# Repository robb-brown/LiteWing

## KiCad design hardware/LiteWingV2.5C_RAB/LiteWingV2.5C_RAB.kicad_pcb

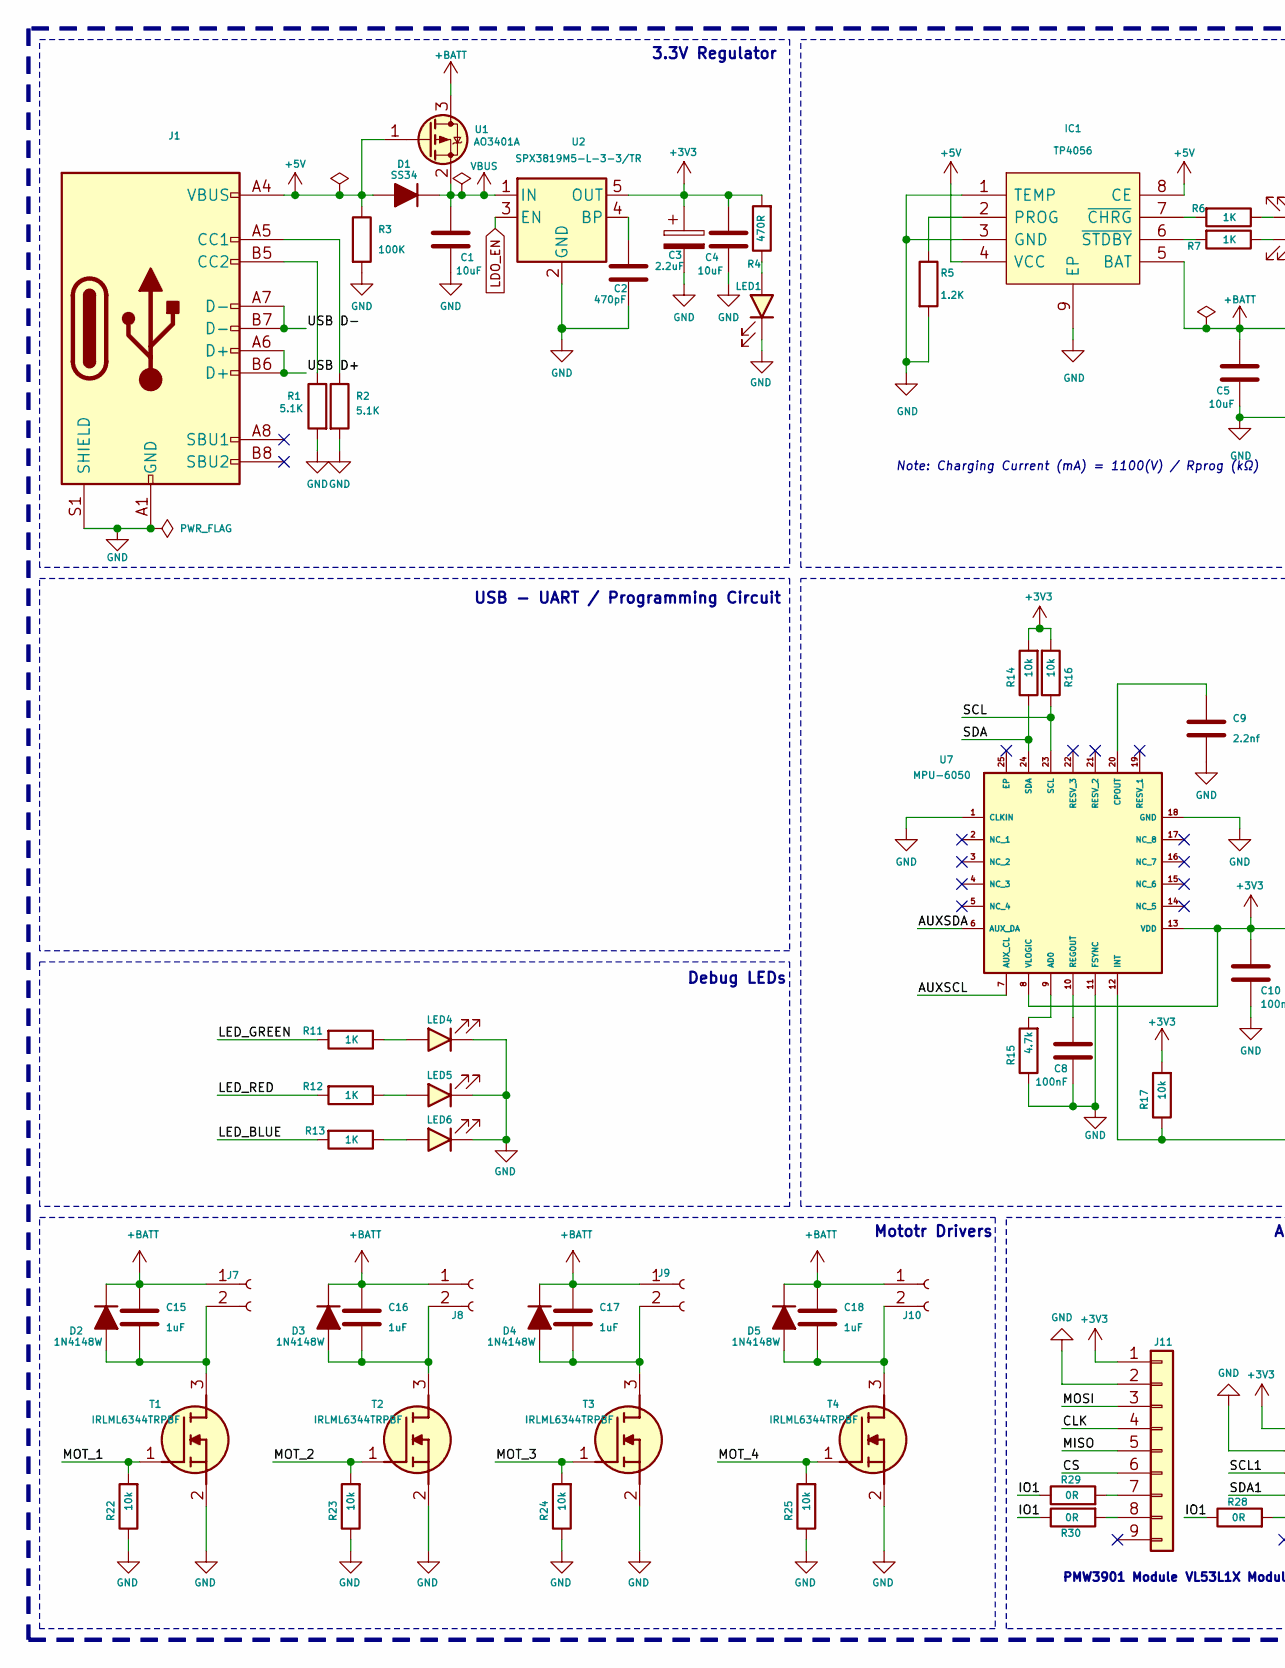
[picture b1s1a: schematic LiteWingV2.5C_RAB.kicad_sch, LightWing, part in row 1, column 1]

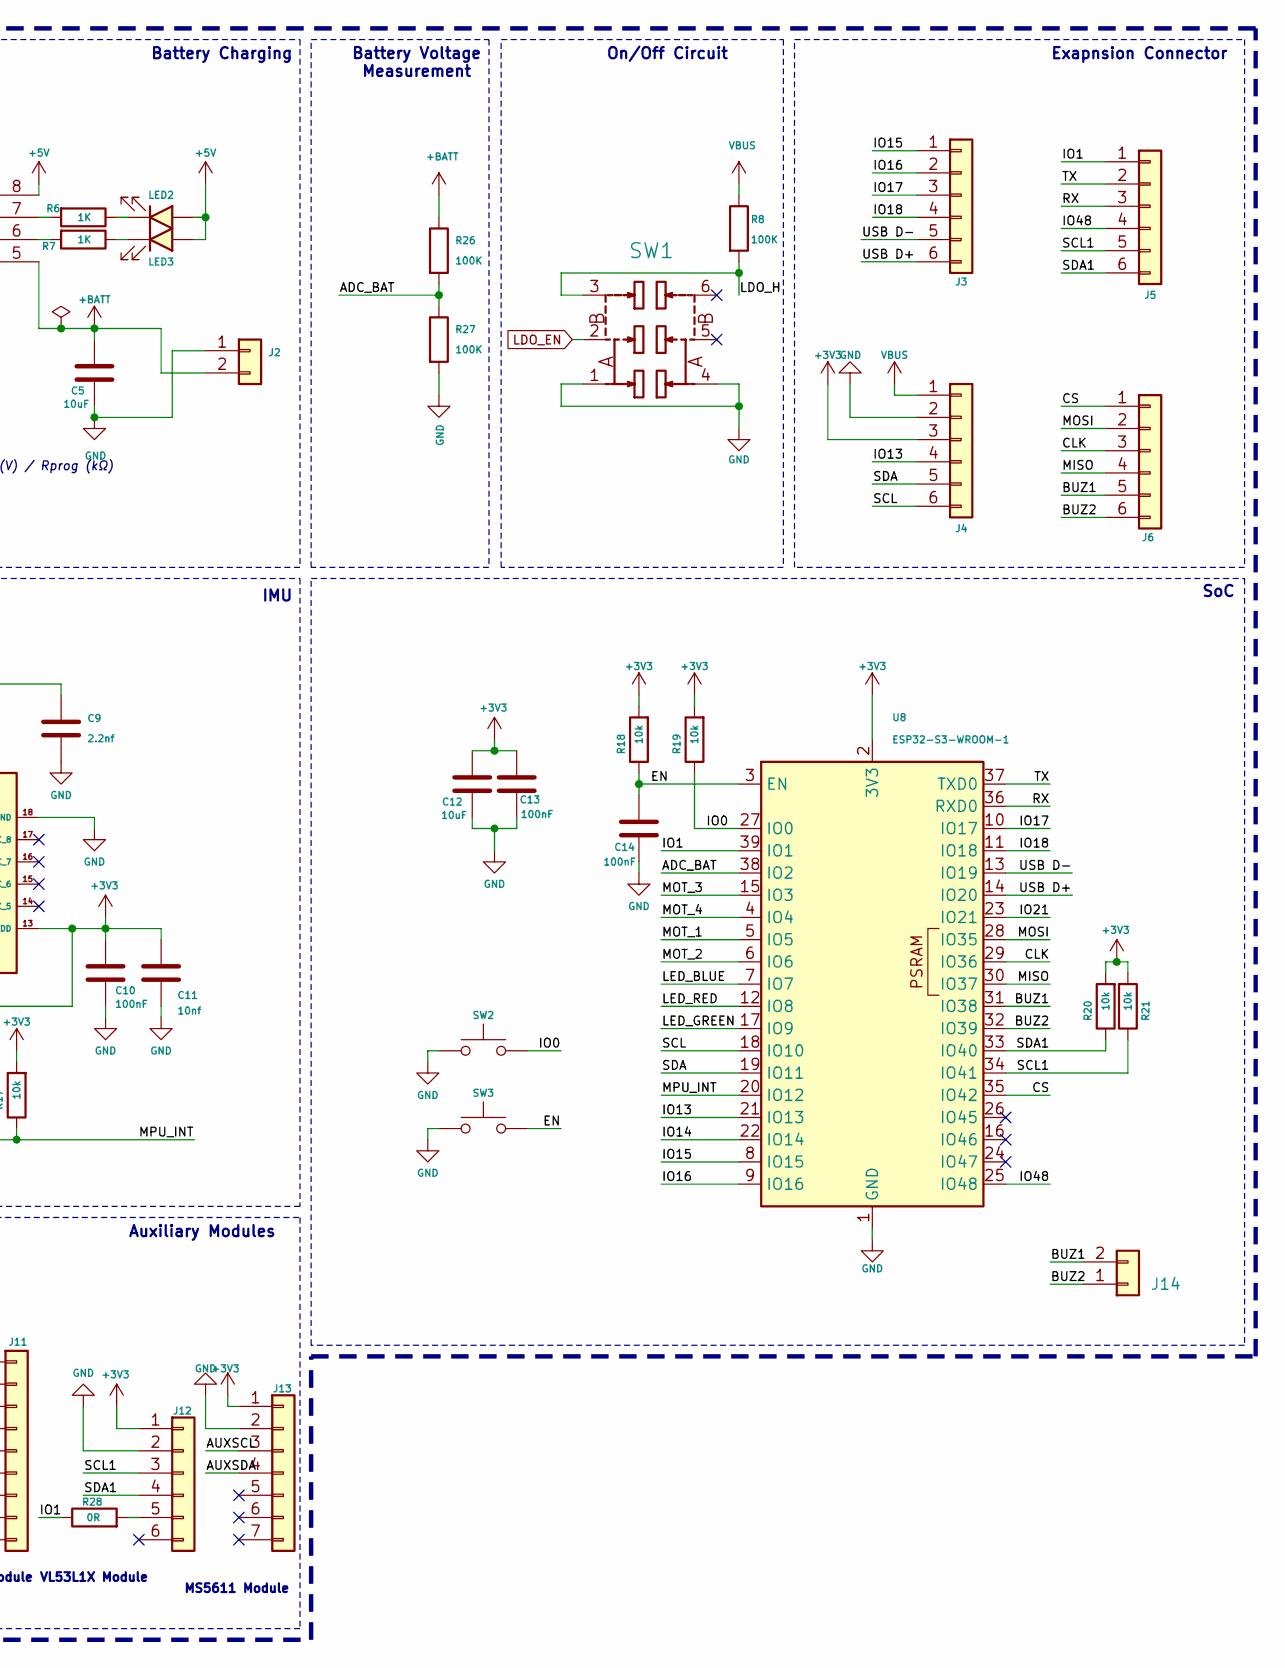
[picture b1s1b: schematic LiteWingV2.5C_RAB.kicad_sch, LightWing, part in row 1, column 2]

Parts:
C1, C4, C5, C12: 10uF; C_0603_1608Metric; MFR.Part # CL10A106KP8NNNC; LCSC Part # C19702
C2: 470pF; C_0603_1608Metric; MFR.Part # 0603B471K500NT; LCSC Part # C1620
C3: 2.2uF; C_0805_2012Metric; MFR.Part # TCC0805X7R225M250FT; LCSC Part # C5448893
C8, C10, C13, C14: 100nF; C_0603_1608Metric; MFR.Part # CC0603KRX7R9BB104; LCSC Part # C14663
C9: 2.2nf; C_0603_1608Metric; MFR.Part # 0603B222K500NT; LCSC Part # C1604
C11: 10nf; C_0603_1608Metric; MFR.Part # 0603B103K500NT; LCSC Part # C57112
C15, C16, C17, C18: 1uF; C_0603_1608Metric; MFR.Part # CL10A105KB8NNNC; LCSC Part # C15849
D1: SS34; D_SMA; MFR.Part # SS34; LCSC Part # C8678
D2, D3, D4, D5: 1N4148W; D_SOD-123F; MFR.Part # 1N4148W; LCSC Part # C81598
IC1: TP4056; SOIC127P600X175-9N; MFR.Part # TP4056; LCSC Part # C20199357
J1: USB_C_Receptacle_USB2.0_16P; USB_C_Receptacle_G-Switch_GT-USB-7010ASV; LCSC Part # C2988369
J2: JST XH 2P 2.50mm SMD Hoz; CONN-TH_2P-P2.50_XH-2AW; MFR.Part # XH-2AW; LCSC Part # C33132
J3, J4, J5, J6: Conn_01x06; PinHeader_1x06_P2.54mm_Vertical
J7, J8, J9, J10: Conn_01x02_Female; JST_PH_B2B-PH-K_1x02_P2.00mm_Vertical
J11: Conn_01x09; PMW3901
J12: Conn_01x06; VL53L1X_BREAKOUT
J13: Conn_01x07; MS5611_Module
J14: Conn_01x02; CONN-TH_1.25T-2A_1.25T-2A; MFR.Part # 1.25-2A; LCSC Part # C722594
LED1, LED2, LED5: LED_Red; LED_0603_1608Metric; MFR.Part # KT-0603R; LCSC Part # C2286
LED3, LED6: LED_Blue; LED_0603_1608Metric; MFR.Part # KT-0603B; LCSC Part # C2288
LED4: LED_Green; LED_0603_1608Metric; MFR.Part # LTST-C193TGKT-5A; LCSC Part # C12065
R1, R2: 5.1K; R_0603_1608Metric; MFR.Part # 0603WAF5101T5E; LCSC Part # C23186
R3, R8, R26, R27: 100K; R_0603_1608Metric; MFR.Part # 0603WAF1003T5E; LCSC Part # C25803
R4: 470R; R_0603_1608Metric; MFR.Part # 0603WAF4700T5E; LCSC Part # C23179
R5: 1.2K; R_0603_1608Metric; MFR.Part # 0603WAF1201T5E; LCSC Part # C22765
R6, R7, R11, R12, R13: 1K; R_0603_1608Metric; MFR.Part # 0603WAF1001T5E; LCSC Part # C21190
R14, R16, R17, R18, R19, R20, R21, R22, R23, R24, R25: 10k; R_0603_1608Metric; MFR.Part # 0603WAF1002T5E; LCSC Part # C25804
R15: 4.7k; R_0603_1608Metric; MFR.Part # 0603WAF4701T5E; LCSC Part # C23162
R28, R29, R30: 0R; R_0603_1608Metric; MFR.Part # 0603WAF0000T5E; LCSC Part # C21189
SW1: MST22D18G2_125; SW-SMD_MST22D18G2; MFR.Part # MST22D18G2 125; LCSC Part # C2906280
SW2, SW3: Tactile Switch 3x4x2; Tactile 3x4x2mm TS-A010; MFR.Part # TS-KG88C-ART25F; LCSC Part # C2874433
T1, T2, T3, T4: IRLML6344TRPBF; SOT95P237X112-3N; MFR.Part # IRLML6344TRPBF-HXY; LCSC Part # C6285738
U1: AO3401A; SOT-23; MFR.Part # AO3401A; LCSC Part # C15127
U2: SPX3819M5-L-3-3/TR; SOT-23-5; MFR.Part # SPX3819M5-L-3-3/TR; LCSC Part # C9055
U7: MPU-6050; MPU6050; MFR.Part # MPU-6050; LCSC Part # C24112
U8: ESP32-S3-WROOM-1; MFR.Part # ESP32-S3-WROOM-1-N8; LCSC Part # C2913198

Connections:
+3V3: C3.1, C4.1, C10.1, C11.1, C12.1, C13.1, J4.3, J11.1, J12.1, J13.1, R4.2, R14.2, R16.2, R17.2, R18.2, R19.2, R20.2, R21.2, U2.5 (OUT), U7.8 (VLOGIC), U7.13 (VDD), U8.2 (3V3)
+5V: D1.2 (A), IC1.4 (VCC), IC1.8 (CE), J1.A4 (VBUS), J1.A9 (VBUS), J1.B4 (VBUS), J1.B9 (VBUS), LED2.2 (A), LED3.2 (A), R3.1, U1.1 (G)
+BATT: C5.1, C15.1, C16.1, C17.1, C18.1, D2.1 (K), D3.1 (K), D4.1 (K), D5.1 (K), IC1.5 (BAT), J2.2, J7.1, J8.1, J9.1, J10.1, R26.1, U1.3 (D)
/ADC_BAT: R26.2, R27.1, U8.38 (IO2)
/AUXSCL: J13.3, U7.7 (AUX_CL)
/AUXSDA: J13.4, U7.6 (AUX_DA)
/BUZ1: J6.5, J14.2, U8.31 (IO38)
/BUZ2: J6.6, J14.1, U8.32 (IO39)
/CLK: J6.3, J11.4, U8.29 (IO36)
/CS: J6.1, J11.6, U8.35 (IO42)
/EN: C14.1, R18.1, SW3.2, U8.3 (EN)
/IO0: R19.1, SW2.2, U8.27 (IO0)
/IO1: J5.1, R28.1, R29.1, R30.1, U8.39 (IO1)
/IO13: J4.4, U8.21 (IO13)
/IO14: U8.22 (IO14)
/IO15: J3.1, U8.8 (IO15)
/IO16: J3.2, U8.9 (IO16)
/IO17: J3.3, U8.10 (IO17)
/IO18: J3.4, U8.11 (IO18)
/IO21: U8.23 (IO21)
/IO48: J5.4, U8.25 (IO48)
/LDO_H: R8.2, SW1.3
/LED_BLUE: R13.2, U8.7 (IO7)
/LED_GREEN: R11.2, U8.17 (IO9)
/LED_RED: R12.2, U8.12 (IO8)
/MISO: J6.4, J11.5, U8.30 (IO37)
/MOSI: J6.2, J11.3, U8.28 (IO35)
/MOT_1: R22.2, T1.1 (G), U8.5 (IO5)
/MOT_2: R23.2, T2.1 (G), U8.6 (IO6)
/MOT_3: R24.2, T3.1 (G), U8.15 (IO3)
/MOT_4: R25.2, T4.1 (G), U8.4 (IO4)
/MPU_INT: R17.1, U7.12 (INT), U8.20 (IO12)
/RX: J5.3, U8.36 (RXD0)
/SCL: J4.6, R16.1, U7.23 (SCL), U8.18 (IO10)
/SCL1: J5.5, J12.3, R21.1, U8.34 (IO41)
/SDA: J4.5, R14.1, U7.24 (SDA), U8.19 (IO11)
/SDA1: J5.6, J12.4, R20.1, U8.33 (IO40)
/TX: J5.2, U8.37 (TXD0)
/USB D+: J1.A6 (D+), J1.B6 (D+), J3.6, U8.14 (IO20)
/USB D-: J1.A7 (D-), J1.B7 (D-), J3.5, U8.13 (IO19)
GND: C1.2, C2.2, C3.2, C4.2, C5.2, C8.2, C9.2, C10.2, C11.2, C12.2, C13.2, C14.2, IC1.1 (TEMP), IC1.3 (GND), IC1.9 (EP), J1.A1 (GND), J1.A12 (GND), J1.B1 (GND), J1.B12 (GND), J1.S1 (SHIELD), J2.1, J4.2, J11.2, J12.2, J13.2, LED1.1 (K), LED4.1 (K), LED5.1 (K), LED6.1 (K), R1.2, R2.2, R3.2, R5.2, R15.1, R22.1, R23.1, R24.1, R25.1, R27.2, SW1.1, SW1.4, SW2.1, SW3.1, T1.2 (S), T2.2 (S), T3.2 (S), T4.2 (S), U2.2 (GND), U7.1 (CLKIN), U7.11 (FSYNC), U7.18 (GND), U8.1 (GND), U8.40 (GND), U8.41 (GND)
LDO_EN: SW1.2, U2.3 (EN)
unnamed: C15.2, D2.2 (A), J7.2, T1.3 (D)
unnamed: C16.2, D3.2 (A), J8.2, T2.3 (D)
unnamed: C17.2, D4.2 (A), J9.2, T3.3 (D)
unnamed: C18.2, D5.2 (A), J10.2, T4.3 (D)
unnamed: IC1.2 (PROG), R5.1
unnamed: IC1.7 (~CHRG), R6.2
unnamed: IC1.6 (~STDBY), R7.2
unnamed: J1.A5 (CC1), R2.1
unnamed: J1.B5 (CC2), R1.1
unnamed: J11.7, R29.2
unnamed: J11.8, R30.2
unnamed: J12.5, R28.2
unnamed: LED1.2 (A), R4.1
unnamed: LED2.1 (K), R6.1
unnamed: LED3.1 (K), R7.1
unnamed: LED4.2 (A), R11.1
unnamed: LED5.2 (A), R12.1
unnamed: LED6.2 (A), R13.1
unnamed: C2.1, U2.4 (BP)
unnamed: R15.2, U7.9 (AD0)
unnamed: C9.1, U7.20 (CPOUT)
unnamed: C8.1, U7.10 (REGOUT)
VBUS: C1.1, D1.1 (K), J4.1, R8.1, U1.2 (S), U2.1 (IN)

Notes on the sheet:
Note: Charging Current (mA) = 1100(V) / Rprog (kΩ)
IMU
VL53L1X Module
Debug LEDs
Battery Charging
3.3V Regulator
Battery Voltage Measurement
USB - UART / Programming Circuit
SoC
Mototr Drivers
MS5611 Module
Exapnsion Connector
Auxiliary Modules
On/Off Circuit
PMW3901 Module

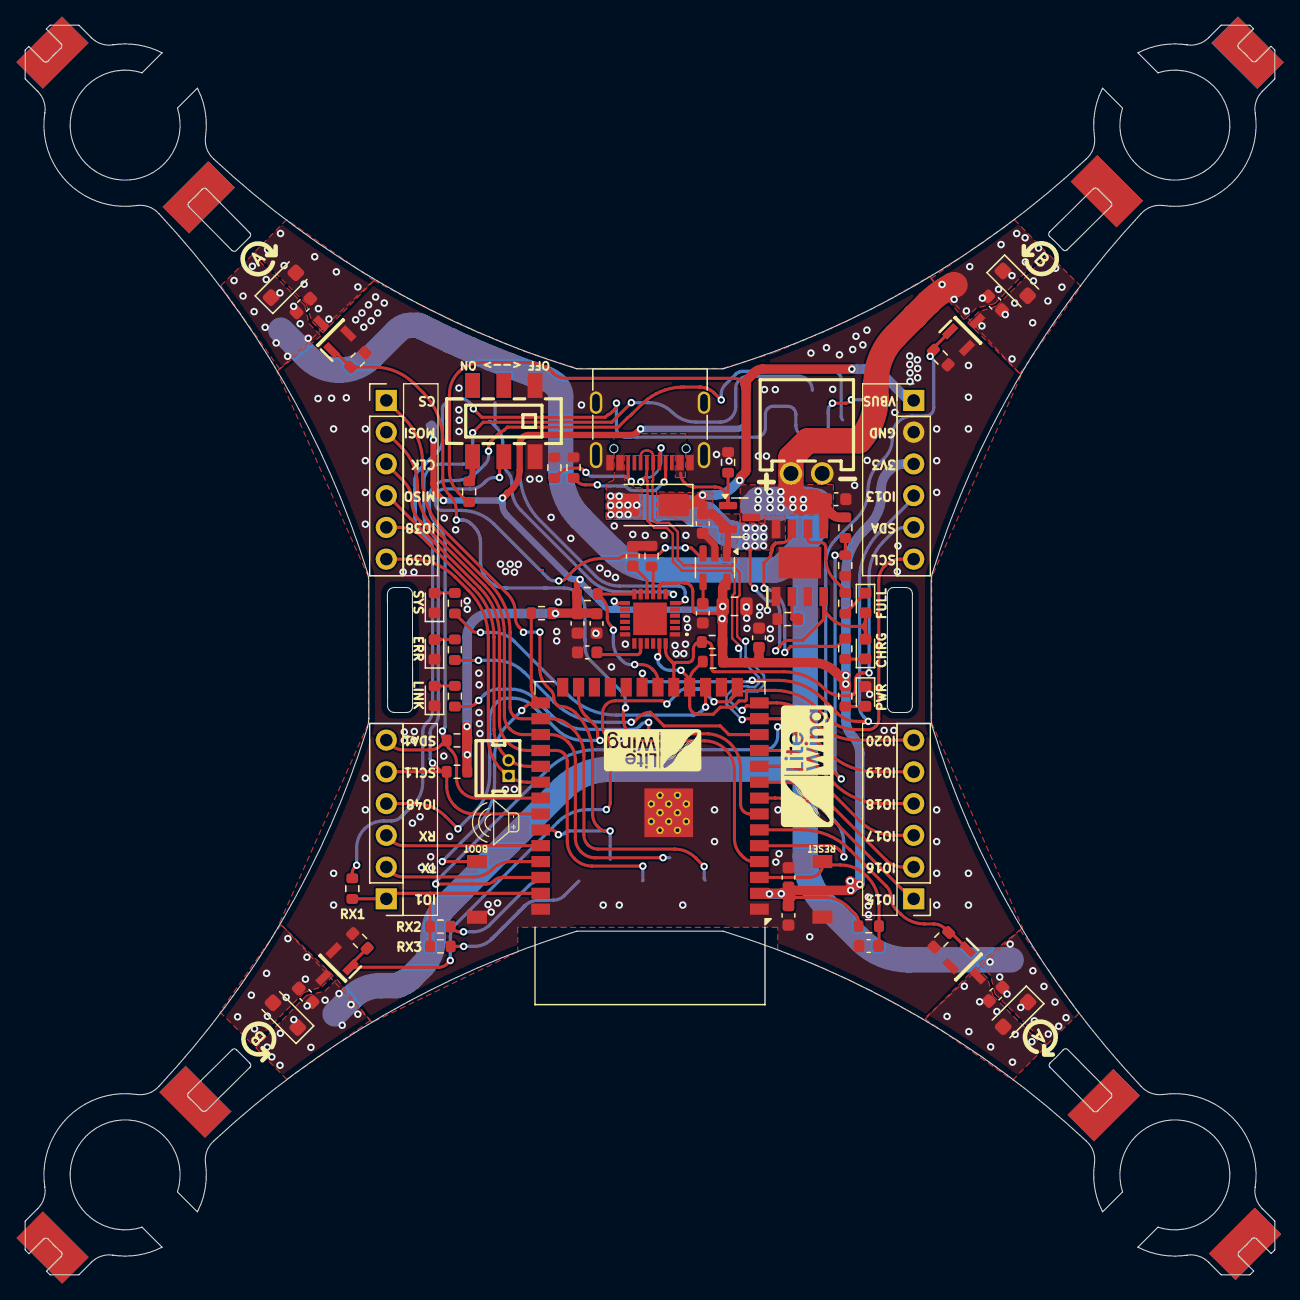
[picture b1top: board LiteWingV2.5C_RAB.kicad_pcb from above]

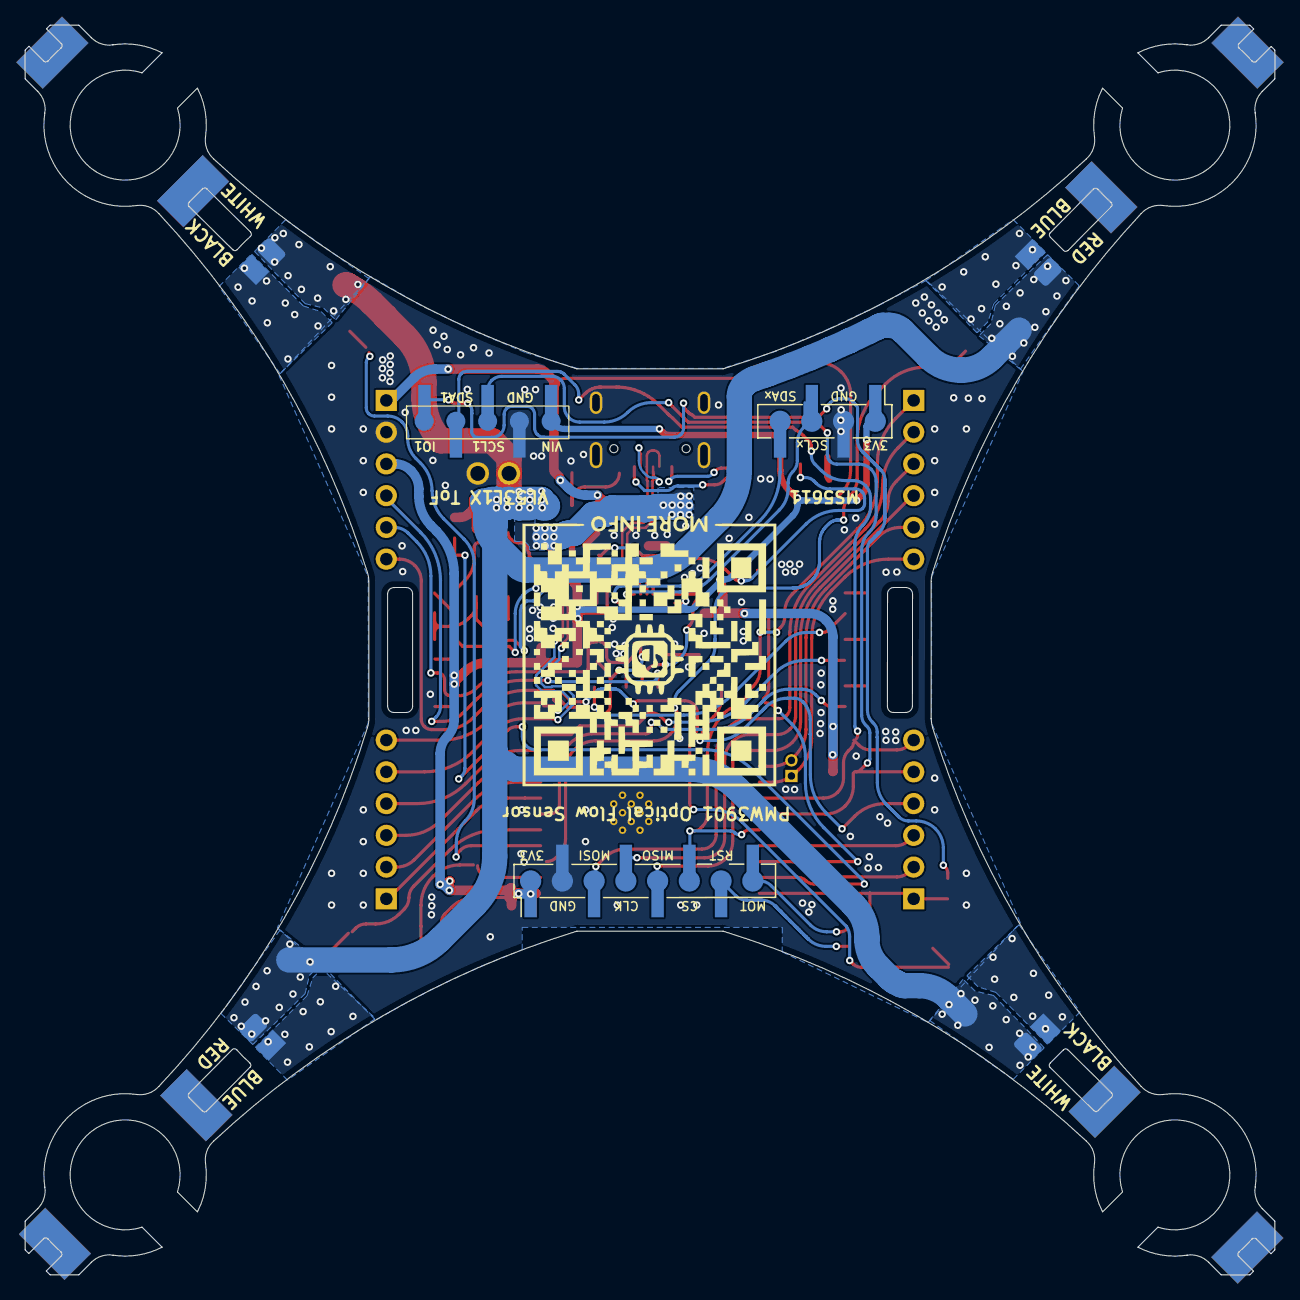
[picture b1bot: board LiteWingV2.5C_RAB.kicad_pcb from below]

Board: 2 copper layers, 100.0 x 100.0 mm, 81 parts (3 on the bottom side), 63 nets.

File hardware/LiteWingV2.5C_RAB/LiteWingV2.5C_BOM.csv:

"Reference","Footprint","Value","MFR.Part #","Manufacturer","Package","Qty","LCSC Part #","JLCA Type","LCSC Link","Datasheet"
"J1","SL_Power:USB_C_Receptacle_G-Switch_GT-USB-7010ASV","USB_C_Receptacle_USB2.0_16P","","","SMD","1","C2988369","Extended","https://www.lcsc.com/product-detail/span-style-background-co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","https://www.lcsc.com/datasheet/lcsc_datasheet_2410010031_DEA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"
"IC1","tp4056:SOIC127P600X175-9N","TP4056","TP4056","YONGYUTAI"," ESOP-8","1","C20199357","Extended","https://www.lcsc.com/product-detail/Battery-Management_YONGY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","https://wmsc.lcsc.com/wmsc/upload/file/pdf/v2/lcsc/231229174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"
"SW2,SW3","3x4x2:Tactile 3x4x2mm TS-A010","Tactile Switch 3x4x2","TS-KG88C-ART25F","Hanbo Electronic","SMD_SW_TACT","2","C2874433","Extended","https://www.lcsc.com/product-detail/Tactile-Switches_Hanbo-E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","https://wmsc.lcsc.com/wmsc/upload/file/pdf/v2/lcsc/221110113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"
"D1","Diode_SMD:D_SMA","SS34","SS34","MDD(Microdiode Semiconductor)","SMA(DO-214AC)","1","C8678","Basic","https://www.lcsc.com/product-detail/Schottky-Diodes_MDD-Micr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","https://www.lcsc.com/datasheet/lcsc_datasheet_2407101107_MDD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"
"U2","Package_TO_SOT_SMD:SOT-23-5","SPX3819M5-L-3-3/TR","SPX3819M5-L-3-3/TR"," MaxLinear"," SOT-23-5","1","C9055","Extended","https://www.lcsc.com/product-detail/Voltage-Regulators-Linea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","https://www.lcsc.com/datasheet/lcsc_datasheet_2304140030_Max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"
"SW1","SlideSwitchSMDTop:SW-SMD_MST22D18G2","MST22D18G2_125","MST22D18G2 125","SHOU HAN","SMD-SW","1","C2906280","Extended","https://www.lcsc.com/product-detail/Slide-Switches_SHOU-HAN-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","https://wmsc.lcsc.com/wmsc/upload/file/pdf/v2/lcsc/211019093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"
"U7","MPU6050:MPU6050","MPU-6050","MPU-6050","TDK InvenSense","QFN-24-EP(4x4)","1","C24112","Extended","https://www.lcsc.com/product-detail/Accelerometers_TDK-Inven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","https://www.lcsc.com/datasheet/lcsc_datasheet_1811071024_TDK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"
"LED1,LED2,LED5","LED_SMD:LED_0603_1608Metric","LED_Red","KT-0603R","Hubei KENTO Elec","LED0603","3","C2286","Basic,Extended","https://www.lcsc.com/product-detail/LED-Indication-Discrete_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","https://www.lcsc.com/datasheet/lcsc_datasheet_1810231112_Hub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"
"LED4","LED_SMD:LED_0603_1608Metric","LED_Green","LTST-C193TGKT-5A","Lite-On","LED0603","1","C12065","Extended","https://www.lcsc.com/product-detail/LED-Indication-Discrete_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","https://www.lcsc.com/datasheet/lcsc_datasheet_1810231514_Lit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"
"LED3,LED6","LED_SMD:LED_0603_1608Metric","LED_Blue","KT-0603B","Hubei KENTO Elec","LED0603","2","C2288","Basic","https://www.lcsc.com/product-detail/LED-Indication-Discrete_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","https://www.lcsc.com/datasheet/lcsc_datasheet_1810220913_Hub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"
"J2","XH2P:CONN-TH_2P-P2.50_XH-2AW","JST XH 2P 2.50mm SMD Hoz","XH-2AW","BOOMELE(Boom Precision Elec)","Push-Pull,P=2.5mm","1","C33132","Extended","https://www.lcsc.com/product-detail/Wire-To-Board-Connector_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","https://www.lcsc.com/datasheet/lcsc_datasheet_2109101230_BOO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"
"T1,T2,T3,T4","SI2302DS-T1:SOT95P237X112-3N","IRLML6344TRPBF","IRLML6344TRPBF-HXY"," HXY MOSFET","SOT-23","4","C6285738 ","Extended","https://www.lcsc.com/product-detail/MOSFETs_HXY-MOSFET-IRLML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","https://www.lcsc.com/datasheet/lcsc_datasheet_2305231118_HXY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"
"U8","RF_Module:ESP32-S3-WROOM-1","ESP32-S3-WROOM-1","ESP32-S3-WROOM-1-N8","Espressif Systems","SMD,18x25.5mm","1","C2913198","Extended","https://www.lcsc.com/product-detail/WiFi-Modules_Espressif-S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","https://wmsc.lcsc.com/wmsc/upload/file/pdf/v2/lcsc/221026143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"
"J14","ConnTH1.25MM:CONN-TH_1.25T-2A_1.25T-2A","Conn_01x02"," 1.25-2A","CAX"," Plugin,P=1.25mm","1"," C722594","Extended","https://www.lcsc.com/product-detail/Wire-To-Board-Connector_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","https://wmsc.lcsc.com/wmsc/upload/file/pdf/v2/lcsc/230414003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"
"U1","Package_TO_SOT_SMD:SOT-23","AO3401A","AO3401A","Alpha & Omega Semicon","SOT-23","1","C15127","Basic","https://www.lcsc.com/product-detail/MOSFETs_Alpha-Omega-Semi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","https://www.lcsc.com/datasheet/lcsc_datasheet_1810171817_Alp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"
"D2,D3,D4,D5","Diode_SMD:D_SOD-123F","1N4148W","1N4148W","ST(Semtech)","SOD-123","4","C81598","Basic","https://www.lcsc.com/product-detail/Switching-Diodes_ST-Semt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","https://www.vishay.com/docs/85748/1n4148w.pdf"
"R3,R8,R26,R27","Resistor_SMD:R_0603_1608Metric","100K","0603WAF1003T5E"," UNI-ROYAL(Uniroyal Elec),UNI-ROYAL(Uniroyal Elec)","R0603","4","C25803","Baic,Basic","https://www.lcsc.com/product-detail/Chip-Resistor-Surface-Mo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","https://www.lcsc.com/datasheet/lcsc_datasheet_2206010045_UNI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"
"R14,R16,R17,R18,R19,R20,R21,R22,R23,R24,R25","Resistor_SMD:R_0603_1608Metric","10k","0603WAF1002T5E","UNI-ROYAL(Uniroyal Elec)","R0603","11"," C25804","Basic","https://www.lcsc.com/product-detail/Chip-Resistor-Surface-Mo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","https://www.lcsc.com/datasheet/lcsc_datasheet_2206010045_UNI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"
"R1,R2","Resistor_SMD:R_0603_1608Metric","5.1K","0603WAF5101T5E","UNI-ROYAL(Uniroyal Elec)","R0603","2","C23186","Basic","https://www.lcsc.com/product-detail/Chip-Resistor-Surface-Mo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","https://www.lcsc.com/datasheet/lcsc_datasheet_2206010116_UNI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"
"R15","Resistor_SMD:R_0603_1608Metric","4.7k","0603WAF4701T5E","UNI-ROYAL(Uniroyal Elec)","R0603","1","C23162","Basic","https://www.lcsc.com/product-detail/Chip-Resistor-Surface-Mo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","https://www.lcsc.com/datasheet/lcsc_datasheet_2206010116_UNI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"
"R5","Resistor_SMD:R_0603_1608Metric","1.2K","0603WAF1201T5E","UNI-ROYAL(Uniroyal Elec)","R0603","1","C22765","Basic","https://www.lcsc.com/product-detail/Chip-Resistor-Surface-Mo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","https://www.lcsc.com/datasheet/lcsc_datasheet_2206010130_UNI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"
"R6,R7,R11,R12,R13","Resistor_SMD:R_0603_1608Metric","1K","0603WAF1001T5E","UNI-ROYAL(Uniroyal Elec)","R0603","5","C21190","Basic","https://www.lcsc.com/product-detail/Chip-Resistor-Surface-Mo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","https://www.lcsc.com/datasheet/lcsc_datasheet_2206010130_UNI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"
"R4","Resistor_SMD:R_0603_1608Metric","470R","0603WAF4700T5E","UNI-ROYAL(Uniroyal Elec)","R0603","1","C23179","Basic","https://www.lcsc.com/product-detail/Chip-Resistor-Surface-Mo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","https://www.lcsc.com/datasheet/lcsc_datasheet_2206010116_UNI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"
"C1,C4,C5,C12","Capacitor_SMD:C_0603_1608Metric","10uF","CL10A106KP8NNNC","Samsung Electro-Mechanics","C0603","4","C19702","Basic","https://www.lcsc.com/product-detail/Multilayer-Ceramic-Capac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","https://www.lcsc.com/datasheet/lcsc_datasheet_2304140030_Sam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"
"C3","Capacitor_SMD:C_0805_2012Metric","2.2uF","TCC0805X7R225M250FT","CCTC","C0805","1","C5448893","Basic","https://www.lcsc.com/product-detail/Multilayer-Ceramic-Capac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","https://www.lcsc.com/datasheet/lcsc_datasheet_2407101107_MDD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"
"C15,C16,C17,C18","Capacitor_SMD:C_0603_1608Metric","1uF","CL10A105KB8NNNC","Samsung Electro-Mechanics","C0603","4","C15849","Basic","https://www.lcsc.com/product-detail/Multilayer-Ceramic-Capac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","https://www.lcsc.com/datasheet/lcsc_datasheet_2304140030_Sam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"
"C8,C10,C13,C14","Capacitor_SMD:C_0603_1608Metric","100nF","CC0603KRX7R9BB104"," YAGEO","C0603","4","C14663","Basic","https://www.lcsc.com/product-detail/Multilayer-Ceramic-Capac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","https://www.lcsc.com/datasheet/lcsc_datasheet_2211101700_YAG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"
"C11","Capacitor_SMD:C_0603_1608Metric","10nf","0603B103K500NT","FH (Guangdong Fenghua Advanced Tech)","C0603","1","C57112","Basic","https://www.lcsc.com/product-detail/Multilayer-Ceramic-Capac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","https://www.lcsc.com/datasheet/lcsc_datasheet_2304140030_FH-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"
"C9","Capacitor_SMD:C_0603_1608Metric","2.2nf","0603B222K500NT"," FH (Guangdong Fenghua Advanced Tech)","C0603","1","C1604","Basic","https://www.lcsc.com/product-detail/Multilayer-Ceramic-Capac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","https://www.lcsc.com/datasheet/lcsc_datasheet_2304140030_FH-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"
"C2","Capacitor_SMD:C_0603_1608Metric","470pF","0603B471K500NT"," FH (Guangdong Fenghua Advanced Tech)","C0603","1","C1620","Basic","https://www.lcsc.com/product-detail/Multilayer-Ceramic-Capac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","https://www.lcsc.com/datasheet/lcsc_datasheet_2304140030_FH-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"
"R28,R29,R30","Resistor_SMD:R_0603_1608Metric","0R","0603WAF0000T5E","UNI-ROYAL(Uniroyal Elec)","R0603","3"," C21189","Basic","https://www.lcsc.com/product-detail/Chip-Resistor-Surface-Mo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","https://www.lcsc.com/datasheet/lcsc_datasheet_2206010130_UNI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"

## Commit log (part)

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2025-12-26 Update to remove USB to serial converter and use native USB on ESP32-S3 instead.
